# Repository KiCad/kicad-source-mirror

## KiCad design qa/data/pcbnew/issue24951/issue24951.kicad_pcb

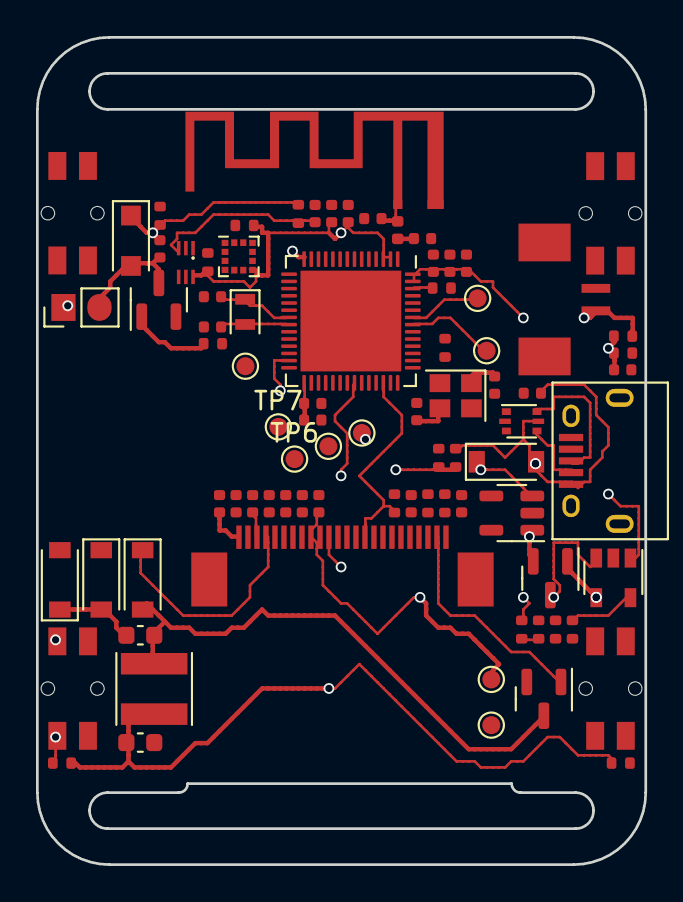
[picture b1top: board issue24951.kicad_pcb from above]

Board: 4 copper layers, 33.8 x 46.0 mm, 84 parts (0 on the bottom side), 53 nets.

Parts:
AE1: Antenna_Chip; SWRA117D
C1, C10: 10uF; C_0402_1005Metric
C2, C3, C4, C15: 1uF; C_0402_1005Metric
C5, C6, C11, C12, C13, C14: 100nF; C_0402_1005Metric
C7, C9: TBD; C_0402_1005Metric
C16, C19: 22pF; C_0402_1005Metric
C17, C18: 18pF; C_0402_1005Metric
C20, C21: 4.7uF/50V; C_0603_1608Metric
C22, C23, C24, C25, C26, C27, C28, C29: 1uF/50V; C_0402_1005Metric
D1, D3, D4, D5: MBR0530; D_SOD-123
D2: 1N4001; D_SOD-123F
J1: Battery; 1.25T-2PWT (Molex 532610271)
J2: Micro USB; USB_Micro-B
J3: FPC24(0.5MM); 24_Pins_0.5mm_Pitch_ZIF_Connector_UP
L1: TBD; L_0402_1005Metric
L2: 47uH 0.5A; L_Taiyo-Yuden_NR-40xx
M1: Vibration_Motor; Motor_Header
OFSDUP1: GND; TestPoint_Pad_D1.0mm
OFSDUP2: 3V3; TestPoint_Pad_D1.0mm
Q1: CJ2301; SOT-23
Q2: S8050; SOT-23
Q3: AO3400A; SOT-23
R1, R3, R18, R20: 10K; R_0402_1005Metric
R2, R4, R6, R7, R8, R10, R11, R15, R19: 100K; R_0402_1005Metric
R5, R14: 51K; R_0402_1005Metric
R9: 360K; R_0402_1005Metric
R12: TBD; R_0402_1005Metric
R13: 1K; R_0402_1005Metric
R16: 1M; R_0402_1005Metric
R17: 2.2; R_0402_1005Metric
SW1: BTN2; EVQPUC
SW2: BTN1; EVQPUC
SW3: BTN3; EVQPUC
SW4: BTN4; EVQPUC
TP1: TX; TestPoint_Pad_D1.0mm
TP2: RX; TestPoint_Pad_D1.0mm
TP3: BOOT; TestPoint_Pad_D1.0mm
TP4: 3V3; TestPoint_Pad_D1.0mm
TP5: GND; TestPoint_Pad_D1.0mm
TP6: SCL; TestPoint_Pad_D1.0mm
TP7: SDA; TestPoint_Pad_D1.0mm
U1: SR2HARU
U2: RT908033; SOT-23-5
U3: TP4054; SOT-23-5
U4: ESP32-S3; QFN-56-1EP_7x7mm_P0.4mm_EP5.6x5.6mm
U5: USBLC6-2P6; SOT-666
U6: BMA423; LGA-12_2x2mm_P0.5mm
Y1: 32.768KHz; Crystal_SMD_2012-2Pin_2.0x1.2mm
Y2: 40MHz; Crystal_SMD_2520-4Pin_2.5x2.0mm

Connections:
+3V3: C1.1, C3.1, C4.1, C5.1, C6.1, C10.1, C14.1, C20.1, C28.1, D2.1 (K), J3.15, J3.16, L2.2, M1.1 (+), OFSDUP2.1, R1.2, R4.2, R7.2, R10.2, R11.2, R18.2, R19.1, R20.2, TP4.1, U1.6 (VCC), U2.5 (VOUT), U4.2 (VDD3P3), U4.3 (VDD3P3), U4.20 (VDD3P3_RTC), U4.46 (VDD3P3_CPU), U4.55 (VDDA), U4.56 (VDDA), U6.3 (VDDIO), U6.7 (VDD), U6.10 (CSB)
+BATT: J1.1, Q1.3 (D), R8.1, U3.3 (VBAT)
/32K_N: C18.1, U4.22 (GPIO16/ADC2_CH5/XTAL_32K_N), Y1.2
/32K_P: C17.1, U4.21 (GPIO15/ADC2_CH4/XTAL_32K_P), Y1.1
/40M_N: C19.1, U4.53 (XTAL_N), Y2.3
/40M_P: C16.1, R12.2, Y2.1
ACC_INT_1: U4.19 (GPIO14/ADC2_CH3), U6.5 (INT1)
ACC_INT_2: U4.18 (GPIO13/ADC2_CH2), U6.6 (INT2)
ADC: C11.1, R8.2, R9.1, U4.14 (GPIO9/ADC1_CH8)
BTN1: R4.1, SW2.1 (A), U4.12 (GPIO7/ADC1_CH6)
BTN2: R7.1, SW1.1 (A), U1.2 (~SR1), U4.11 (GPIO6/ADC1_CH5)
BTN3: R10.1, SW3.1 (A), TP3.1, U1.5 (~SR0), U4.5 (GPIO0/BOOT)
BTN4: R11.1, SW4.1 (A), U4.13 (GPIO8/ADC1_CH7)
BUSY: J3.9, U4.41 (GPIO36)
CS: J3.12, U4.38 (GPIO33)
DC: J3.11, U4.39 (GPIO34)
DN: J2.2 (D-), U5.4 (I/O2)
DP: J2.3 (D+), U5.6 (I/O1)
EN: C2.1, R1.1, U1.3 (~RST), U4.4 (CHIP_PU/RESET)
GDR: J3.2, Q3.1 (G), R16.1
GND: AE1.2 (PCB_Trace), C1.2, C2.2, C3.2, C4.2, C5.2, C6.2, C7.2, C9.2, C10.2, C11.2, C12.2, C13.2, C15.2, C16.2, C17.2, C18.2, C19.2, C20.2, C22.2, C23.2, C24.2, C25.2, C26.2, C27.2, C28.2, C29.1, D4.1 (K), J1.2, J2.5 (GND), J3.8, J3.17, OFSDUP1.1, Q2.2 (E), R2.2, R3.1, R9.2, R15.2, R16.2, R17.1, SW1.2 (B), SW2.2 (B), SW3.2 (B), SW4.2 (B), TP5.1, U1.1 (VSS), U2.2 (GND), U3.2 (VSS), U4.57 (GND), U5.2 (GND), U6.1 (SDO), U6.8 (GNDIO), U6.9 (GND), Y2.2, Y2.4
MOSI: J3.14, U4.36 (SPICLK_N/GPIO48)
unnamed: AE1.1 (FEED), C7.1, L1.1
unnamed: D1.1 (K), Q1.2 (S), U2.1 (VIN), U2.3 (EN)
unnamed: C14.2, D2.2 (A), M1.2 (-), Q2.3 (C)
unnamed: C21.1, D3.1 (K), D4.2 (A)
unnamed: C21.2, D5.2 (A), L2.1, Q3.3 (D)
unnamed: C23.1, J3.5
unnamed: C24.1, J3.18
unnamed: C25.1, J3.20
unnamed: C26.1, J3.22
unnamed: C27.1, J3.24
unnamed: Q2.1 (B), R13.1
unnamed: R3.2, U3.5 (PROG)
unnamed: R6.2, U3.1 (STAT)
unnamed: C9.1, L1.2, U4.1 (LNA_IN/RF)
unnamed: TP2.1, U4.50 (U0RXD/PROG/GPIO44)
unnamed: TP1.1, U4.49 (U0TXD/PROG/GPIO43)
unnamed: R12.1, U4.54 (XTAL_P)
PREVGH: C22.1, D5.1 (K), J3.21
PREVGL: C29.2, D3.2 (A), J3.23
RES: J3.10, R19.2, U4.40 (GPIO35)
RESE: J3.3, Q3.2 (S), R17.2
SCK: J3.13, U4.37 (SPICLK_P/GPIO47)
SCL: R20.1, TP6.1, U4.16 (GPIO11/ADC2_CH0), U6.12 (SCX)
SDA: R18.1, TP7.1, U4.17 (GPIO12/ADC2_CH1), U6.2 (SDX)
STAT: R5.2, R6.1, U4.15 (GPIO10/ADC1_CH9)
USB_D+: U4.26 (GPIO20/USB_D+/ADC2_CH9), U5.1 (I/O1)
USB_D-: U4.25 (GPIO19/USB_D-/ADC2_CH8), U5.3 (I/O2)
USB_DET: R14.2, R15.1, U4.27 (GPIO21)
VBUS: C12.1, D1.2 (A), J2.1 (VBUS), Q1.1 (G), R2.1, R5.1, R14.1, U3.4 (VDD), U5.5 (VBUS)
VDD: C13.1, C15.1, U4.29 (VDD_SPI)
VIB_PWM: R13.2, U4.23 (GPIO17/ADC2_CH6/DAC_2)
